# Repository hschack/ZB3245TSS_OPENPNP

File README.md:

More to come
Link
Mellow Fly Super8Pro
https://teamgloomy.github.io/fly_super8pro_h723_general_3_5.html

to bay
https://www.aliexpress.com/item/1005004431621335.htm

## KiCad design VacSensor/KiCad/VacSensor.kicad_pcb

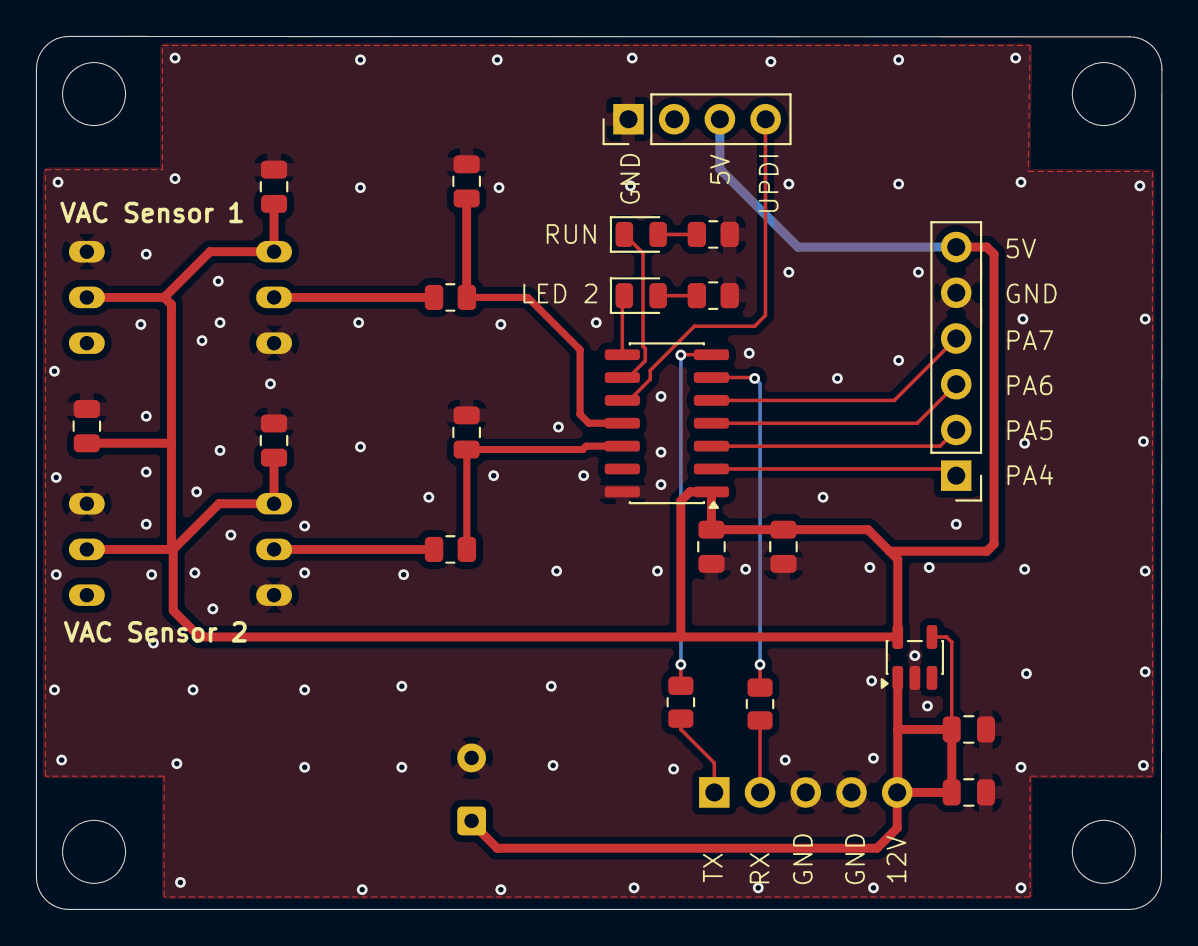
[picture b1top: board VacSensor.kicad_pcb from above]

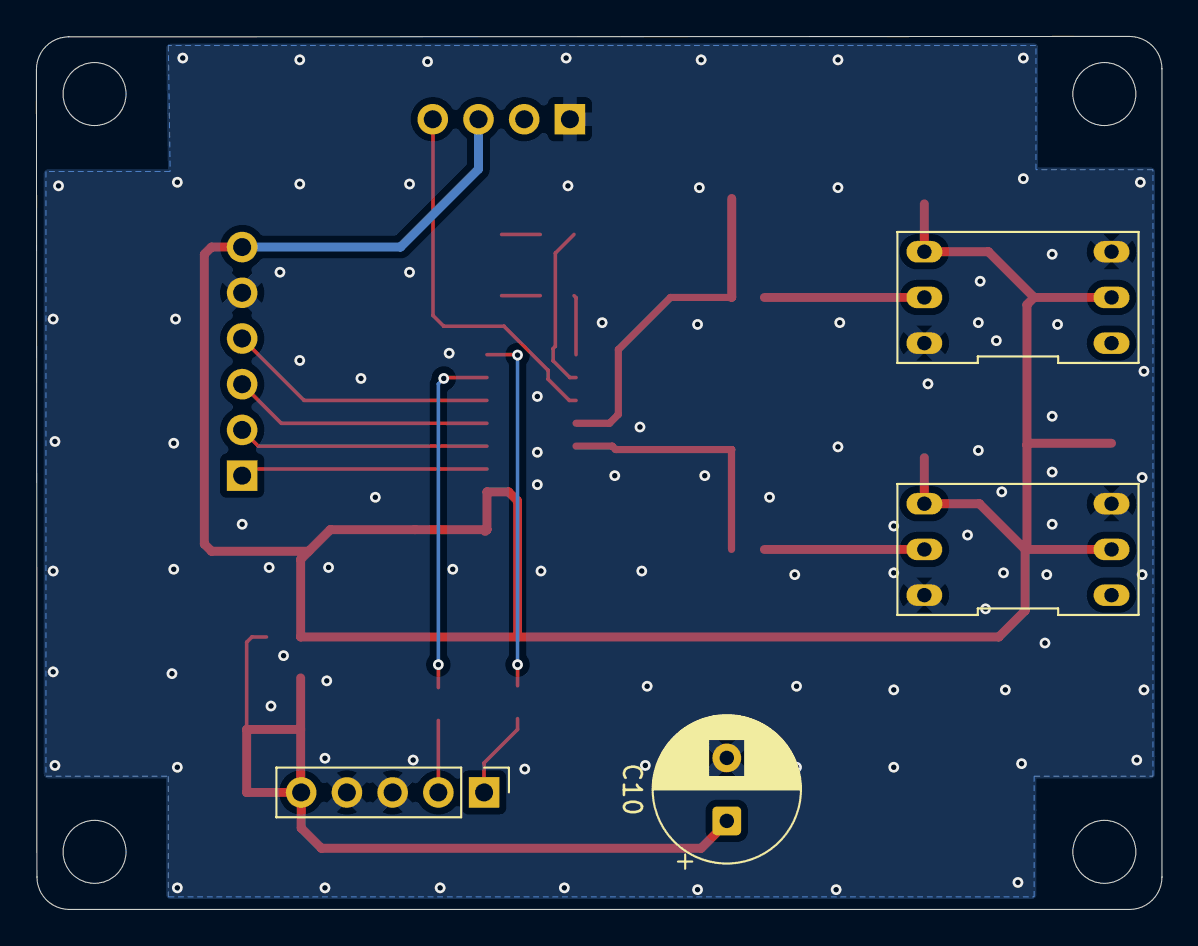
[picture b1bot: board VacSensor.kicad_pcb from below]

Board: 2 copper layers, 62.5 x 48.5 mm, 25 parts (4 on the bottom side), 20 nets.

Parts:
C1, C3, C4, C5, C6, C7, C9: 100n; C_0805_2012Metric
C2, C8: 10u; C_0805_2012Metric
C10: C_Polarized; CP_Radial_D8.0mm_P3.50mm
D1, D2: LED; D_0805_2012Metric
J1: Conn_01x05_Pin; PinHeader_1x05_P2.54mm_Vertical
J2: Conn_01x04_Pin; PinHeader_1x04_P2.54mm_Vertical
J3: Conn_01x06_Pin; PinHeader_1x06_P2.54mm_Vertical
R1, R2: 2k2; R_0805_2012Metric
R3, R4: 1k; R_0805_2012Metric
R5, R6: 100; R_0805_2012Metric
U1, U2: XGZP6859A; DIP-6_VAC_Sensor
U3: ATtiny3224-SS; SOIC-14_3.9x8.7mm_P1.27mm
U4: MCP1804x-5002xOT; SOT-23-5

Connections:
+5V: C1.1, C2.1, C5.2, C6.2, C7.1, J2.3, J3.6, U1.2 (VDD), U1.4 (VDD), U2.2 (VDD), U2.4 (VDD), U3.1 (VCC), U4.5 (VOUT)
+12V: C8.1, C9.1, C10.1, J1.5, U4.1 (VIN), U4.4 (~SHDN)
/RX: J1.2, R6.2
/TX: J1.1, R5.2
/UPDI: J2.4, U3.10 (~RESET/PA0)
GND: C1.2, C2.2, C3.1, C4.1, C5.1, C6.1, C7.2, C8.2, C9.2, C10.2, J1.3, J1.4, J2.1, J3.5, R3.2, R4.2, U1.3 (GND), U1.6 (GND), U2.3 (GND), U2.6 (GND), U3.14 (GND), U4.2 (GND)
unnamed: D1.2 (A), R3.1
unnamed: D1.1 (K), U3.9 (PB0)
unnamed: D2.2 (A), R4.1
unnamed: D2.1 (K), U3.8 (PB1)
unnamed: J3.1, U3.2 (PA4)
unnamed: J3.2, U3.3 (PA5)
unnamed: J3.3, U3.4 (PA6)
unnamed: J3.4, U3.5 (PA7)
unnamed: R1.1, U1.5 (OUT)
unnamed: R2.1, U2.5 (OUT)
unnamed: C3.2, R1.2, U3.11 (PA1)
unnamed: C4.2, R2.2, U3.12 (PA2)
unnamed: R5.1, U3.7 (PB2)
unnamed: R6.1, U3.6 (PB3)

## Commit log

2026-05-18 Med sdcard h723
2026-06-20 Add links and information to README.md
2026-06-20 Picture
2026-06-20 HQ_Picture
2026-06-20 clean
2026-06-21 DUET3 config.g updatet
